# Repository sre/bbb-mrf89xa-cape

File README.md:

# Beaglebone Black Cape for MRF89XA RF Chip

This is a cape for the MRF89XA RF chip using the 868 MHz ISM band.
It has an onboard antenna, which is good enough for short range
communication. Otherwise and SMA connector can be used to connect
an external amplifier/antenna.

The MRF89XA is connected to the Beaglebone SPI interface and the
relevant control lines are connected to GPIOs. Additionally the
cape has support to drive a SK6812 or WS2812 LED via SPI.

## Image

## Kernel

A matching devicetree overlay can be found in the dt-overlay
directory. Neither the MRF89XA nor the RGB LED currently have
an in-kernel driver. It is possible to access them via userspace
via the spidev module like this:

```
# load spidev kernel module
modprobe spidev
# tell kernel to use spidev driver for both mrf89xa interfaces
echo spidev > /sys/bus/spi/devices/spi0.0/driver_override
echo spi0.0 > /sys/bus/spi/drivers/spidev/bind
echo spidev > /sys/bus/spi/devices/spi0.1/driver_override
echo spi0.1 > /sys/bus/spi/drivers/spidev/bind
echo spidev > /sys/bus/spi/devices/spi0.2/driver_override
echo spi0.2 > /sys/bus/spi/drivers/spidev/bind

```
Afterwards the SPI devices are available as `/dev/spidev0.0`
(mrf89xa data), `/dev/spidev0.1` (mrf89xa cfg) and `/dev/spidev0.2`
(RGB led).

## License

https://creativecommons.org/licenses/by-sa/4.0/

CC-BY-SA 2022 Sebastian Reichel <sre@mainframe.io>

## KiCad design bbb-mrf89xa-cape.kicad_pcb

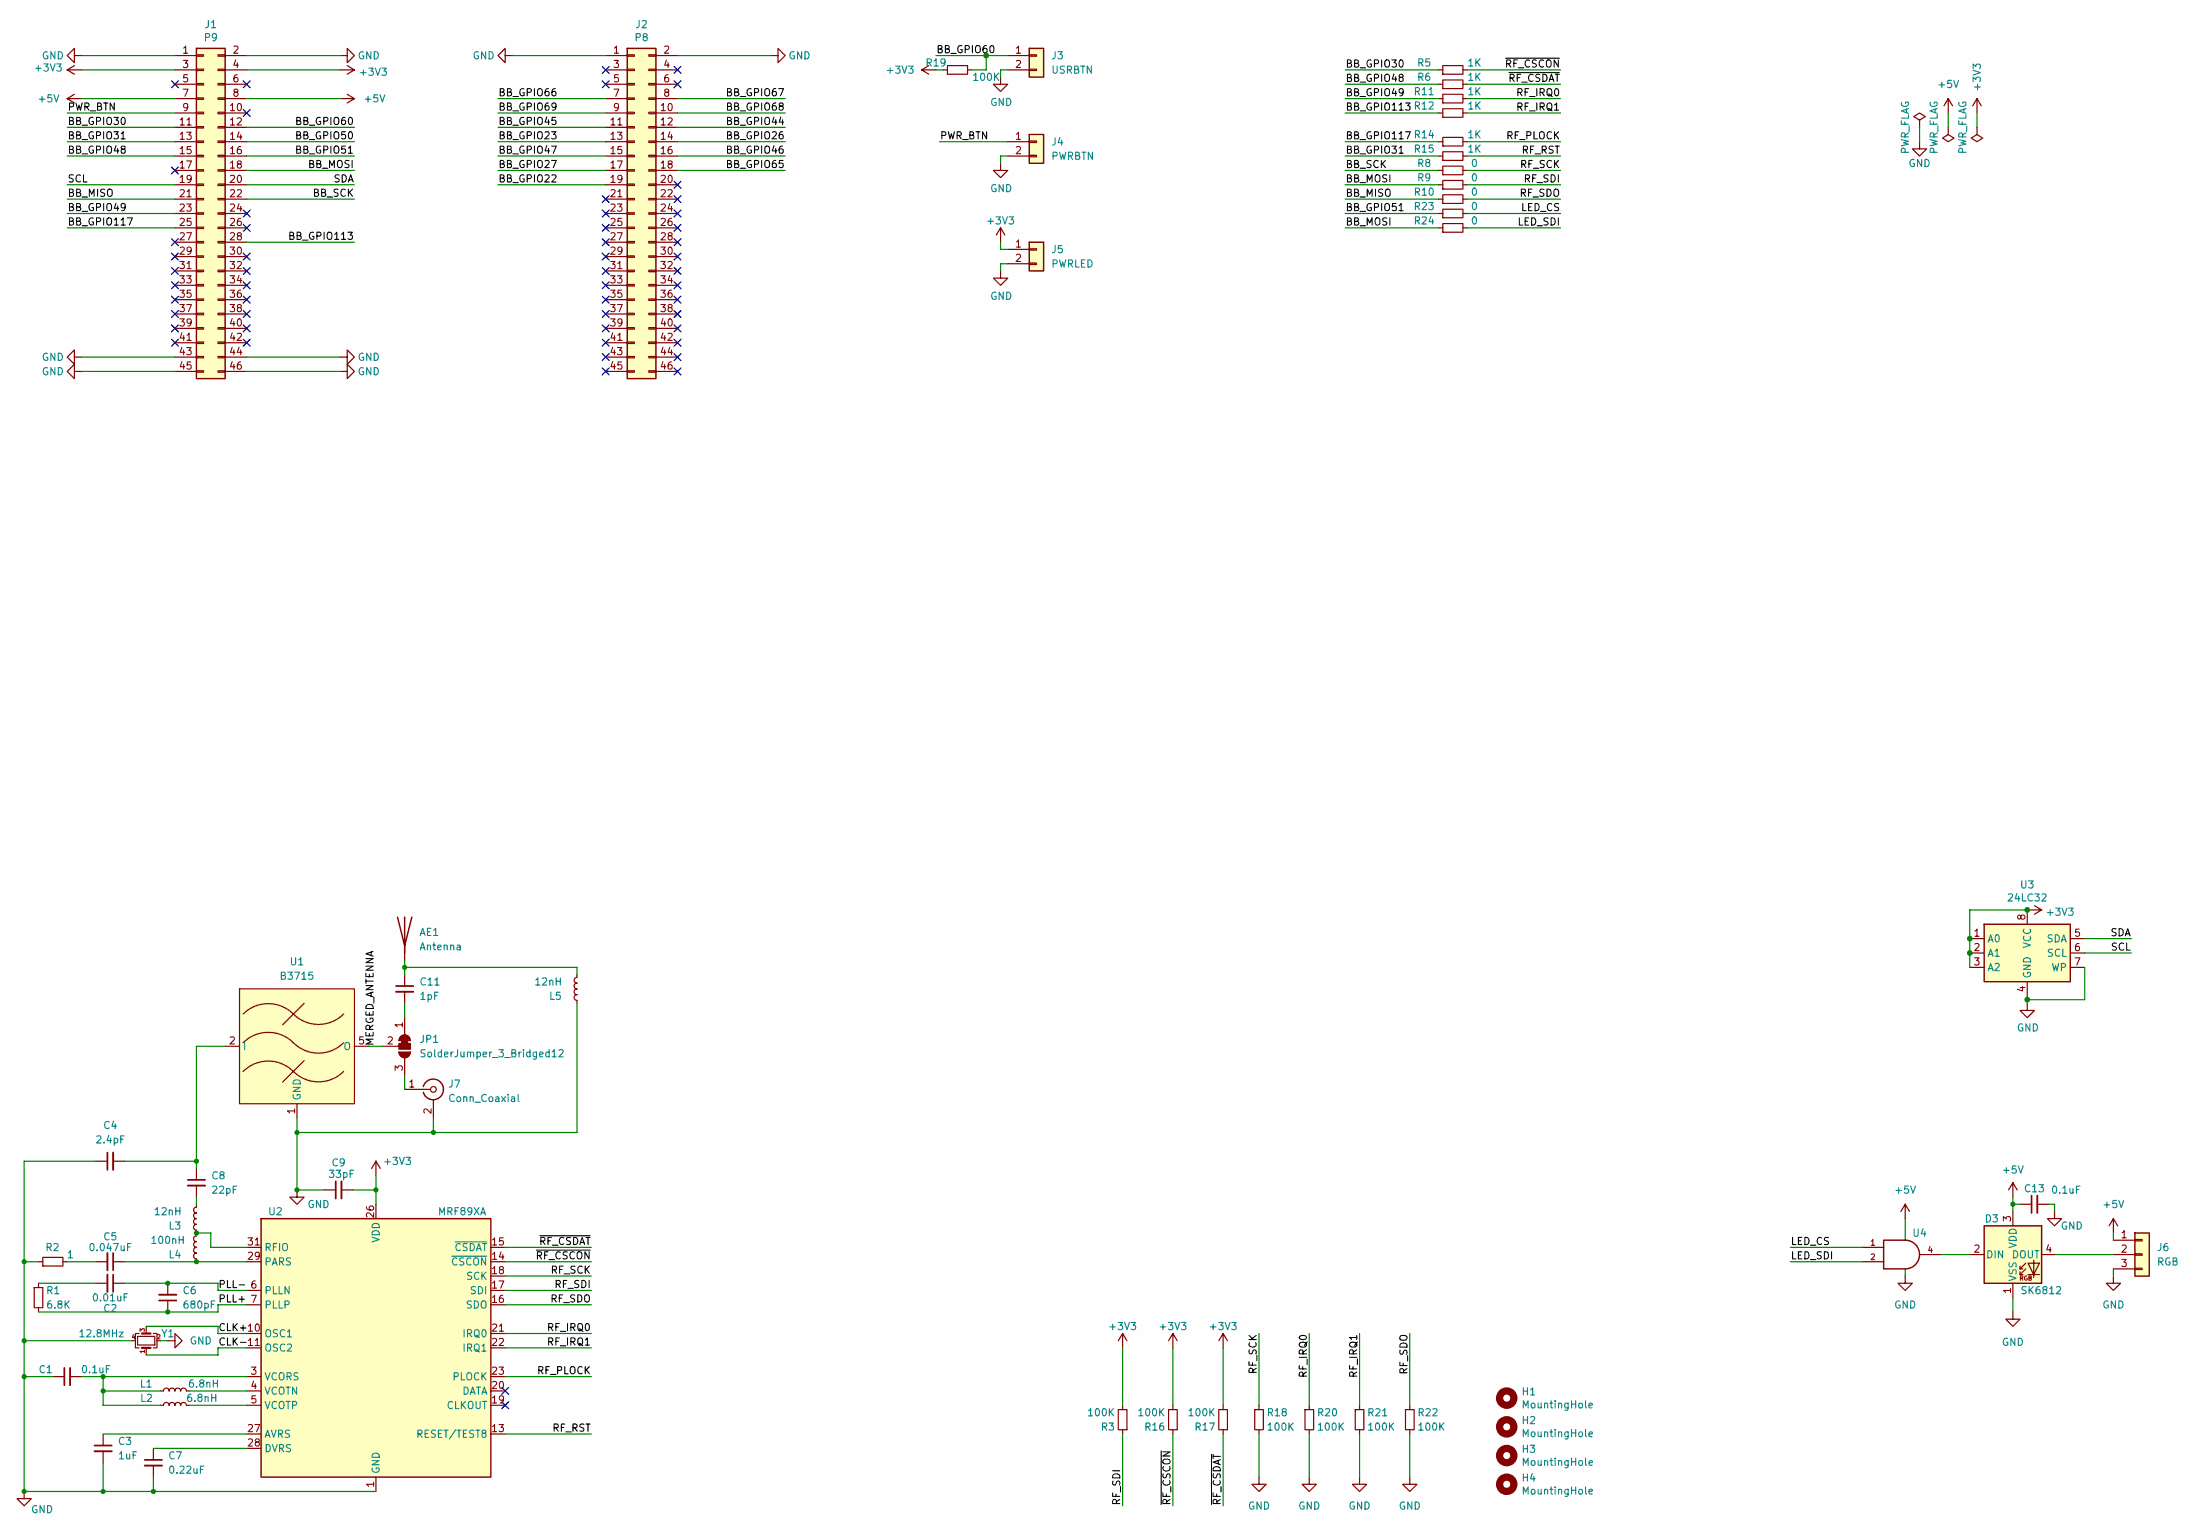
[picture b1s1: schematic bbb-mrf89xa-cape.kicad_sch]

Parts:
AE1: Antenna; Texas_SWRA416_868MHz_915MHz
C1, C13: 0.1uF; C_0603_1608Metric
C2: 0.01uF; C_0603_1608Metric
C3: 1uF; C_0603_1608Metric
C4: 2.4pF; C_0603_1608Metric
C5: 0.047uF; C_0603_1608Metric
C6: 680pF; C_0603_1608Metric
C7: 0.22uF; C_0603_1608Metric
C8: 22pF; C_0603_1608Metric
C9: 33pF; C_0603_1608Metric
C11: 1pF; C_0603_1608Metric
D3: SK6812; LED_SK6812_PLCC4_5.0x5.0mm_P3.2mm
H1, H2, H3, H4: MountingHole; MountingHole_4.3mm_M4
J1: P9; PinHeader_2x23_P2.54mm_Vertical
J2: P8; PinHeader_2x23_P2.54mm_Vertical
J3: USRBTN; PinHeader_1x02_P2.54mm_Vertical
J4: PWRBTN; PinHeader_1x02_P2.54mm_Vertical
J5: PWRLED; PinHeader_1x02_P2.54mm_Vertical
J6: RGB; PinHeader_1x03_P2.54mm_Vertical
J7: Conn_Coaxial; SMA_Amphenol_132291_Vertical
JP1: SolderJumper_3_Bridged12; SolderJumper-3_P1.3mm_Bridged12_RoundedPad1.0x1.5mm_NumberL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
L1, L2: 6.8nH; L_0603_1608Metric
L3, L5: 12nH; L_0603_1608Metric
L4: 100nH; L_0603_1608Metric
R1: 6.8K; R_0603_1608Metric
R2: 1; R_0603_1608Metric
R3, R16, R17, R18, R19, R20, R21, R22: 100K; R_0603_1608Metric
R5, R6, R11, R12, R14, R15: 1K; R_0603_1608Metric
R8, R9, R10, R23, R24: 0; R_0603_1608Metric
U1: B3715; DCC6C_3x3mm
U2: MRF89XA; QFN-32-1EP_5x5mm_P0.5mm_EP3.1x3.1mm
U3: 24LC32; SOIC-8_3.9x4.9mm_P1.27mm
U4: (no value)
Y1: 12.8MHz; Oscillator_SMD_EuroQuartz_XO53-4Pin_5.0x3.2mm

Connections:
+3V3: C9.2, J1.3, J1.4, J5.1, R3.2, R16.2, R17.2, R19.1, U2.26 (VDD), U3.1 (A0), U3.2 (A1), U3.3 (A2), U3.8 (VCC)
+5V: C13.1, D3.3 (VDD), J1.7, J1.8, J6.1, U4.5 (VCC)
/BB_GPIO22: J2.19
/BB_GPIO23: J2.13
/BB_GPIO26: J2.14
/BB_GPIO27: J2.17
/BB_GPIO30: J1.11, R5.1
/BB_GPIO31: J1.13, R15.1
/BB_GPIO44: J2.12
/BB_GPIO45: J2.11
/BB_GPIO46: J2.16
/BB_GPIO47: J2.15
/BB_GPIO48: J1.15, R6.1
/BB_GPIO49: J1.23, R11.1
/BB_GPIO50: J1.14
/BB_GPIO51: J1.16, R23.1
/BB_GPIO60: J1.12, J3.1, R19.2
/BB_GPIO65: J2.18
/BB_GPIO66: J2.7
/BB_GPIO67: J2.8
/BB_GPIO68: J2.10
/BB_GPIO69: J2.9
/BB_GPIO113: J1.28, R12.1
/BB_GPIO117: J1.25, R14.1
/BB_MISO: J1.21, R10.1
/BB_MOSI: J1.18, R9.1, R24.1
/BB_SCK: J1.22, R8.1
/CLK+: U2.10 (OSC1), Y1.3
/CLK-: U2.11 (OSC2), Y1.1
/LED_CS: R23.2, U4.1
/LED_SDI: R24.2, U4.2
/MERGED_ANTENNA: JP1.2 (C), U1.5 (O)
/PLL+: C6.1, R1.2, U2.7 (PLLP)
/PLL-: C2.1, C6.2, U2.6 (PLLN)
/PWR_BTN: J1.9, J4.1
/RF_IRQ0: R11.2, R20.1, U2.21 (IRQ0)
/RF_IRQ1: R12.2, R21.1, U2.22 (IRQ1)
/RF_PLOCK: R14.2, U2.23 (PLOCK)
/RF_RST: R15.2, U2.13 (RESET/TEST8)
/RF_SCK: R8.2, R18.1, U2.18 (SCK)
/RF_SDI: R3.1, R9.2, U2.17 (SDI)
/RF_SDO: R10.2, R22.1, U2.16 (SDO)
/SCL: J1.19, U3.6 (SCL)
/SDA: J1.20, U3.5 (SDA)
/~RF_CSCON: R5.2, R16.1, U2.14 (~CSCON)
/~RF_CSDAT: R6.2, R17.1, U2.15 (~CSDAT)
GND: C1.1, C3.2, C4.1, C7.2, C9.1, C13.2, D3.1 (VSS), J1.1, J1.2, J1.43, J1.44, J1.45, J1.46, J2.1, J2.2, J3.2, J4.2, J5.2, J6.3, J7.2 (Ext), L5.1, R2.1, R18.2, R20.2, R21.2, R22.2, U1.1 (GND), U1.3 (GND), U1.4 (GND), U1.6 (GND), U2.1 (GND), U2.2 (GND), U2.8 (GND), U2.9 (GND), U2.12 (GND), U2.24 (GND), U2.25 (GND), U2.30 (GND), U2.32 (GND), U2.33 (GND), U3.4 (GND), U3.7 (WP), U4.3 (GND), Y1.2, Y1.4
unnamed: AE1.1 (A), C11.1, L5.2
unnamed: C1.2, L1.1, L2.1, U2.3 (VCORS)
unnamed: C2.2, R1.1
unnamed: C3.1, U2.27 (AVRS)
unnamed: C4.2, C8.1, U1.2 (I)
unnamed: C5.1, L4.1, U2.29 (PARS)
unnamed: C5.2, R2.2
unnamed: C7.1, U2.28 (DVRS)
unnamed: C8.2, L3.2
unnamed: C11.2, JP1.1 (A)
unnamed: D3.2 (DIN), U4.4
unnamed: D3.4 (DOUT), J6.2
unnamed: J7.1 (In), JP1.3 (B)
unnamed: L1.2, U2.4 (VCOTN)
unnamed: L2.2, U2.5 (VCOTP)
unnamed: L3.1, L4.2, U2.31 (RFIO)

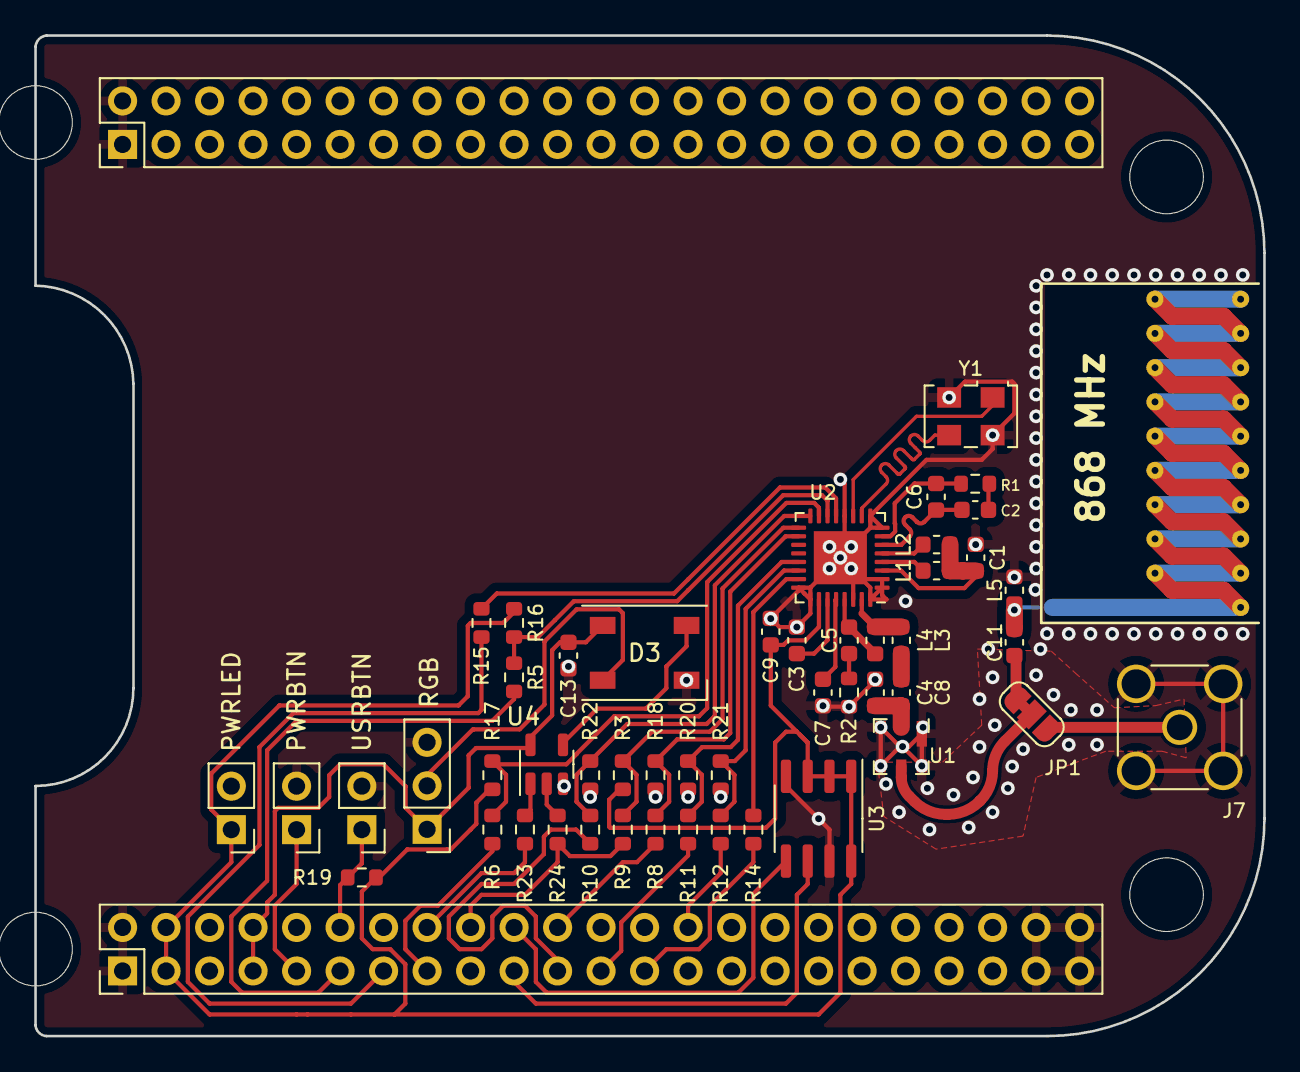
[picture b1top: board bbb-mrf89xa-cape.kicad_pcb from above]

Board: 2 copper layers, 71.8 x 58.4 mm, 56 parts (1 on the bottom side), 49 nets.

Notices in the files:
bbb-mrf89xa-cape.kicad_pcb:
CC-BY-SA © 2022 Sebastian Reichel
